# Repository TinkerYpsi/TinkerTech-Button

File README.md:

# TinkerTech Button
### A PCB for TinkerTech enthusiasts

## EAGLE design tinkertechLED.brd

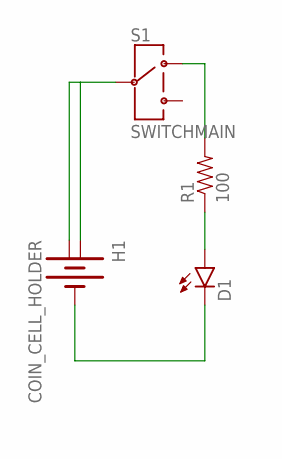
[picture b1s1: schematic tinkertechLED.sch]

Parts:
D1: LED5MM
H1: COIN_CELL_HOLDER
R1: 100; AXIAL-0.3-KIT
S1: SWITCHMAIN; SWITCH

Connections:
unnamed: H1.P$2 (+), H1.P$3 (++), S1.P$2 (C)
unnamed: D1.K (C), H1.P$1 (-)
unnamed: R1.P$2 (2), S1.P$1 (1)
unnamed: D1.A, R1.P$1 (1)

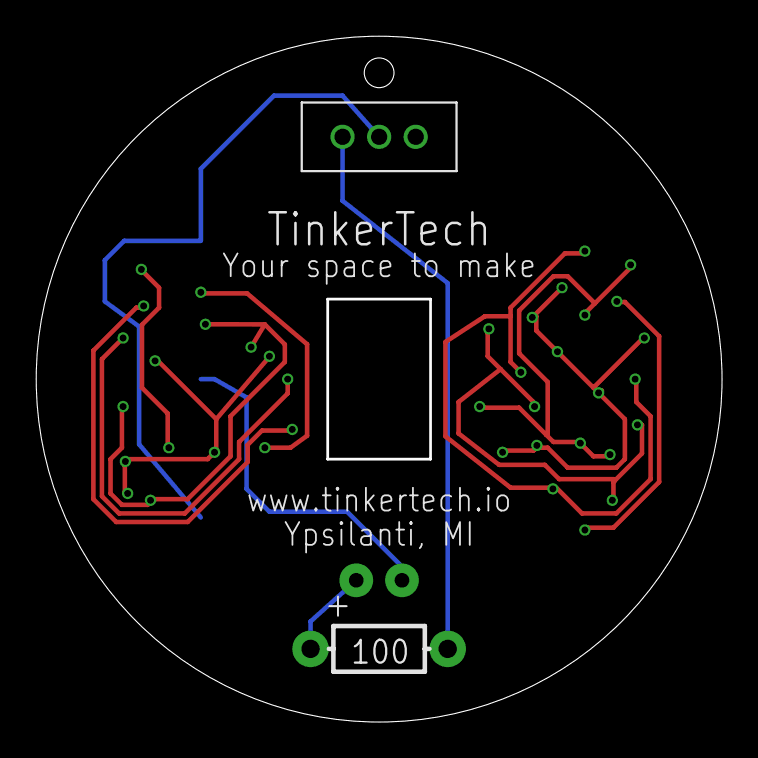
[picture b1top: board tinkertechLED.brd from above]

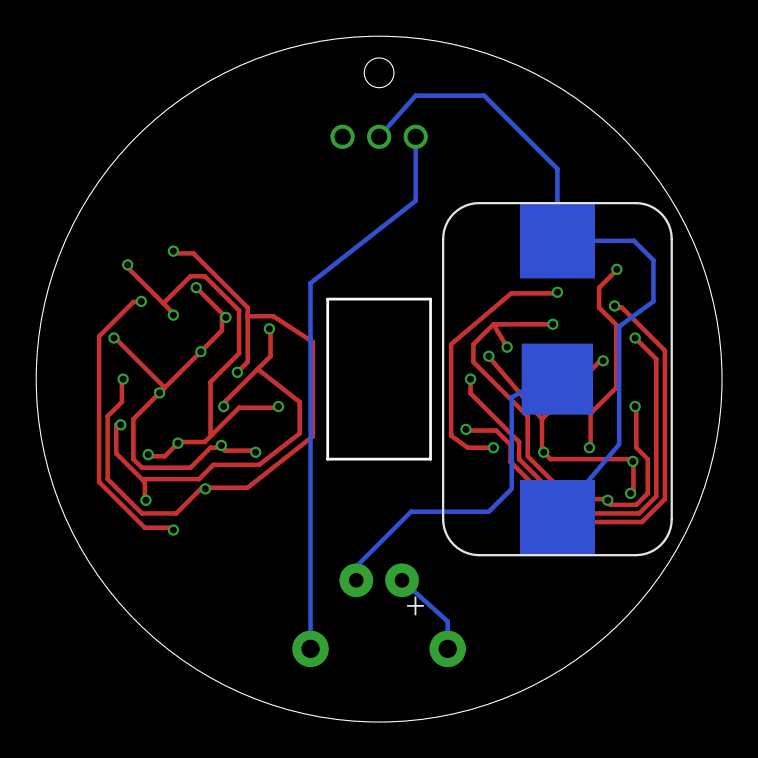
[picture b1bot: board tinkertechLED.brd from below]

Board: 2 copper layers, 38.0 x 38.0 mm, 4 parts (2 on the bottom side), 4 nets.

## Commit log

2018-06-21 added eagle files
2018-06-21 updated REAME with pictures
2018-06-21 updated image links
2018-06-21 shrinked images
2018-06-21 increased image size
2018-06-21 updated README image to links
2018-08-02 Final chances before initial production

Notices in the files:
parts and their libraries:
SparkFun-Passives: Licensing: Creative Commons ShareAlike 4.0 International - https://creativecommons.org/licenses/by-sa/4.0
